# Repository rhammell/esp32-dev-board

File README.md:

# esp32-dev-board
This repository contains the KiCad project files for a custom development board based on the ESP32-S3-WROOM module.

The board features a simplistic design, breaking out GPIO and power pins for easy prototyping, while using only essential components for power and data transfer. 

KiCad project files include the schematic and PCB designs which can be viewed and edited, and a full BOM with LCSC part numbers for sourcing and assembly. 

## Features

* **Core:** ESP32-S3-WROOM-1N8R8 module (8MB Flash + 8MB PSRAM).
* **USB Interface:** USB-C connector utilizing the S3's native USB Serial/JTAG controller.
* **Power:** Integrated 3.3V LDO regulator with a dedicated power LED indicator.
* **Prototyping:** Standard 2.54mm pitch header pins for full GPIO and power breakout.
* **Control:** Physical Reset and Boot buttons for manual flashing mode entry.
* **User IO:** Onboard programmable LED tied to **GPIO 21**.
* **Manufacturing:** Complete BOM included with **LCSC part numbers** for simplified sourcing and assembly.

## Changelog

### v0.2
- Replaced LD1117 with AP2114 3.3V regulator for more stable 3.3V power supply
- Transitioned to higher voltage rated 0805 capacitors on power rails to minimize DC bias capacitance loss

### v0.1
- Initial release of the ESP32-S3-WROOM-1 development board.

## Arduino IDE Setup

To program the **ESP32-S3 Dev Board**, follow these steps to configure your environment.

### 1. Install the ESP32 Board Package
1. Open the Arduino IDE (v2.3.6 or newer recommended).
2. Go to **File > Preferences**.
3. In the **Additional Boards Manager URLs** field, paste the following link:
   `https://espressif.github.io/arduino-esp32/package_esp32_index.json`
4. Go to **Tools > Board > Boards Manager**, search for **esp32**, and install the latest version by **Espressif Systems**.

### 2. Required Board Settings
Because this board uses the **N8R8** module with native USB, you must use the following settings in the **Tools** menu:

| Setting            | Selection                          | Reason                                         |
|--------------------|------------------------------------|------------------------------------------------|
| **Board** | **ESP32S3 Dev Module** | Standard target for S3-WROOM modules.         |
| **USB CDC On Boot**| **Enabled** | **Critical:** Allows Serial Monitor over USB. |
| **Flash Mode** | **QIO 80MHz** | Standard for WROOM modules.                    |
| **Flash Size** | **8MB (64Mb)** | Matches the N8 (8MB Flash) specification.      |
| **PSRAM** | **OPI PSRAM** | Matches the R8 (8MB Octal) specification.     |

---

## Hardware Test Sketch

Use this sketch to verify that your PCB is fully functional. It tests the serial communication, identifies the onboard memory, and blinks the onboard LED on **GPIO 21**.

```cpp
/*
 * ESP32-S3 Dev Board Hardware Test
 * Verifies: Native USB Serial, GPIO 21 (LED), and N8R8 Memory
 */

const int USER_LED = 21;

void setup() {
  // Initialize Serial
  // Native USB: Baud rate is ignored but kept for compatibility
  Serial.begin(115200);
  
  // Set LED pin as output
  pinMode(USER_LED, OUTPUT);

  // Wait 2 seconds so you don't miss the initial serial print
  delay(2000); 

  Serial.println("\n========================================");
  Serial.println("   ESP32-S3 CUSTOM DEV BOARD TEST");
  Serial.println("========================================");

  // Print Flash Size
  uint32_t flashSize = ESP.getFlashChipSize() / (1024 * 1024);
  Serial.printf("Flash Size: %d MB\n", flashSize);

  // Print PSRAM Size
  // If this shows 0MB, ensure 'Tools > PSRAM' is set to 'OPI PSRAM'
  uint32_t psramSize = ESP.getPsramSize() / (1024 * 1024);
  Serial.printf("PSRAM Size: %d MB\n", psramSize);

  if (psramSize > 0) {
    Serial.println("Status: PSRAM detected successfully!");
  } else {
    Serial.println("Status: PSRAM NOT FOUND. Check IDE settings.");
  }
  
  Serial.println("----------------------------------------");
  Serial.println("Beginning LED blink on GPIO 21...");
}

void loop() {
  // Toggle LED and print status
  digitalWrite(USER_LED, HIGH);
  Serial.println("LED: ON");
  delay(1000);

  digitalWrite(USER_LED, LOW);
  Serial.println("LED: OFF");
  delay(1000);
}
```

## Troubleshooting 

* **Failed to Connect:** If the IDE cannot find the board, hold the BOOT button, tap the RESET button, and then release BOOT to force the chip into "Download Mode."

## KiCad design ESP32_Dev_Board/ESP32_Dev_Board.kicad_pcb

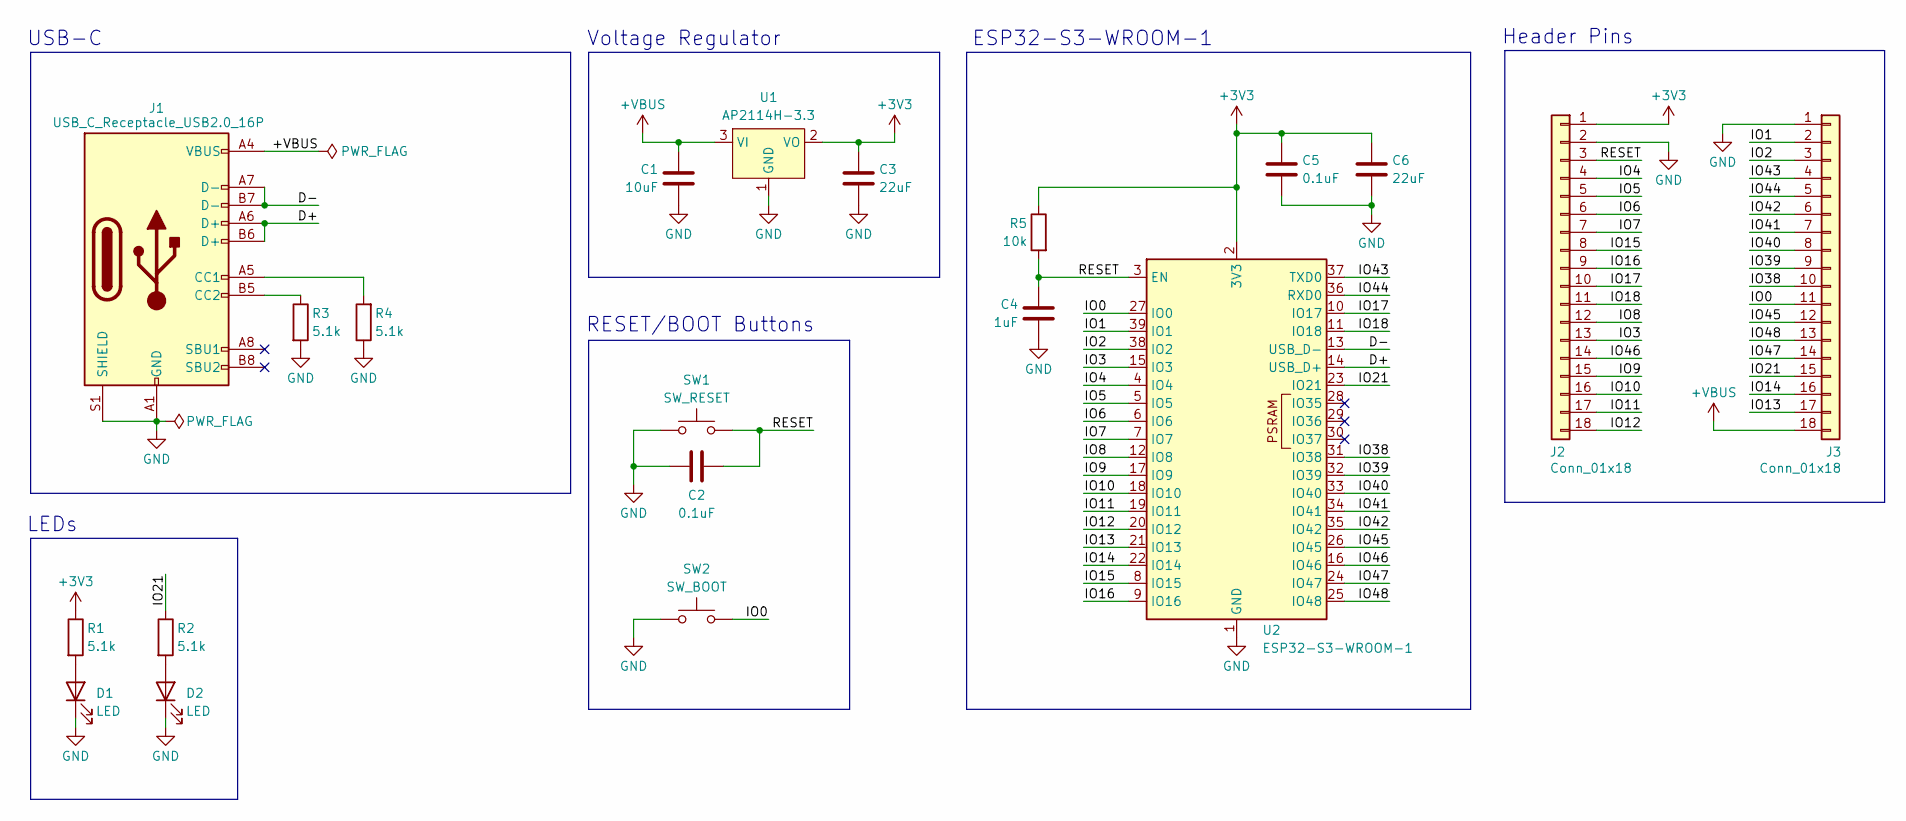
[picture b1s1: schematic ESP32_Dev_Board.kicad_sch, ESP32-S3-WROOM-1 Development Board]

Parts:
C1: 10uF; C_0805_2012Metric; LCSC C15850
C2, C5: 0.1uF; C_0603_1608Metric; LCSC C14663
C3, C6: 22uF; C_0805_2012Metric; LCSC C45783
C4: 1uF; C_0603_1608Metric; LCSC C15849
D1, D2: LED; D_0603_1608Metric; LCSC C2286
J1: USB_C_Receptacle_USB2.0_16P; USB_C_Receptacle_GCT_USB4105-xx-A_16P_TopMnt_Horizontal; LCSC C2988369
J2, J3: Conn_01x18; PinHeader_1x18_P2.54mm_Vertical
R1, R2, R3, R4: 5.1k; R_0603_1608Metric; LCSC C23186
R5: 10k; R_0603_1608Metric; LCSC C25804
SW1: SW_RESET; SW_SPST_TS-1088-xR020; LCSC C720477
SW2: SW_BOOT; SW_SPST_TS-1088-xR020; LCSC C720477
U1: AP2114H-3.3; SOT-223-3_TabPin2; LCSC C150716
U2: ESP32-S3-WROOM-1; LCSC C2913201

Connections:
+3V3: C3.1, C5.1, C6.1, J2.1, R1.1, R5.1, U1.2 (VO), U2.2 (3V3)
+VBUS: C1.1, J1.A4 (VBUS), J1.A9 (VBUS), J1.B4 (VBUS), J1.B9 (VBUS), J3.18, U1.3 (VI)
/D+: J1.A6 (D+), J1.B6 (D+), U2.14 (USB_D+)
/D-: J1.A7 (D-), J1.B7 (D-), U2.13 (USB_D-)
/IO0: J3.11, SW2.2, U2.27 (IO0)
/IO1: J3.2, U2.39 (IO1)
/IO2: J3.3, U2.38 (IO2)
/IO3: J2.13, U2.15 (IO3)
/IO4: J2.4, U2.4 (IO4)
/IO5: J2.5, U2.5 (IO5)
/IO6: J2.6, U2.6 (IO6)
/IO7: J2.7, U2.7 (IO7)
/IO8: J2.12, U2.12 (IO8)
/IO9: J2.15, U2.17 (IO9)
/IO10: J2.16, U2.18 (IO10)
/IO11: J2.17, U2.19 (IO11)
/IO12: J2.18, U2.20 (IO12)
/IO13: J3.17, U2.21 (IO13)
/IO14: J3.16, U2.22 (IO14)
/IO15: J2.8, U2.8 (IO15)
/IO16: J2.9, U2.9 (IO16)
/IO17: J2.10, U2.10 (IO17)
/IO18: J2.11, U2.11 (IO18)
/IO21: J3.15, R2.1, U2.23 (IO21)
/IO38: J3.10, U2.31 (IO38)
/IO39: J3.9, U2.32 (IO39)
/IO40: J3.8, U2.33 (IO40)
/IO41: J3.7, U2.34 (IO41)
/IO42: J3.6, U2.35 (IO42)
/IO43: J3.4, U2.37 (TXD0)
/IO44: J3.5, U2.36 (RXD0)
/IO45: J3.12, U2.26 (IO45)
/IO46: J2.14, U2.16 (IO46)
/IO47: J3.14, U2.24 (IO47)
/IO48: J3.13, U2.25 (IO48)
/RESET: C2.1, C4.1, J2.3, R5.2, SW1.2, U2.3 (EN)
GND: C1.2, C2.2, C3.2, C4.2, C5.2, C6.2, D1.1 (K), D2.1 (K), J1.A1 (GND), J1.A12 (GND), J1.B1 (GND), J1.B12 (GND), J1.S1 (SHIELD), J2.2, J3.1, R3.2, R4.1, SW1.1, SW2.1, U1.1 (GND), U2.1 (GND), U2.40 (GND), U2.41 (GND)
unnamed: D1.2 (A), R1.2
unnamed: D2.2 (A), R2.2
unnamed: J1.A5 (CC1), R4.2
unnamed: J1.B5 (CC2), R3.1

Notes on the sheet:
Voltage Regulator
ESP32-S3-WROOM-1
USB-C
RESET/BOOT Buttons
Header Pins
LEDs

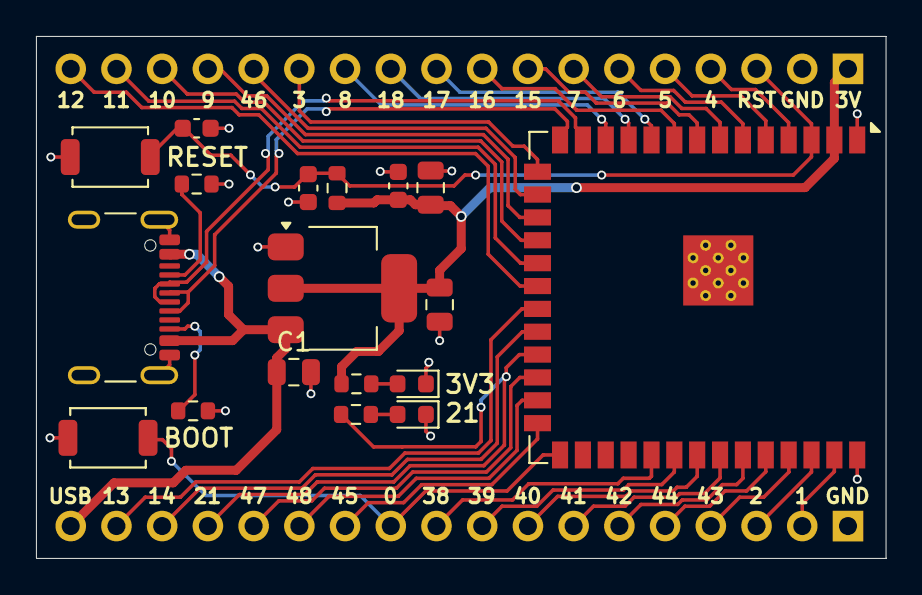
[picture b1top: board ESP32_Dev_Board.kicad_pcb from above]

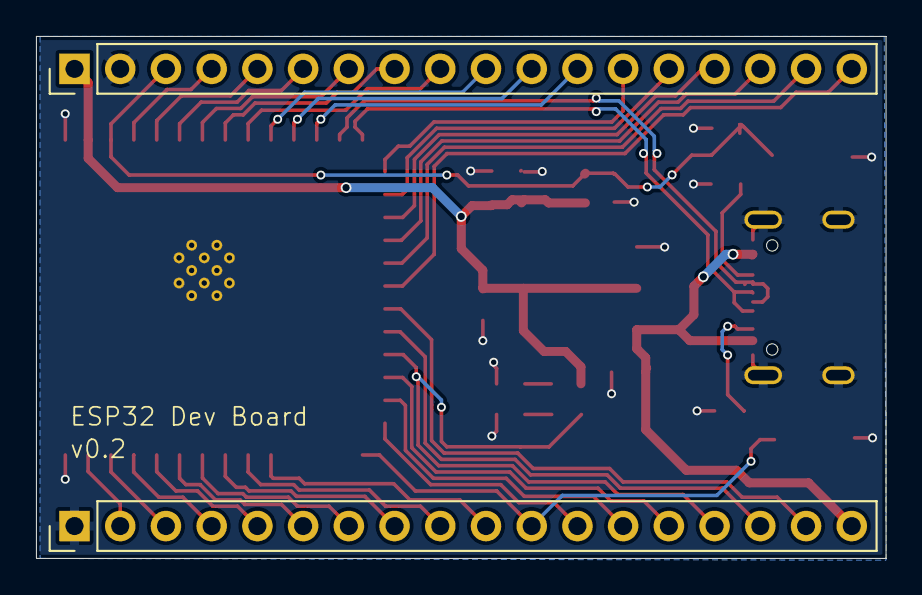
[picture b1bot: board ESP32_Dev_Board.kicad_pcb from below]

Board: 2 copper layers, 47.2 x 29.0 mm, 20 parts (2 on the bottom side), 41 nets.

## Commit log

2025-12-30 Update .gitignore to include macOS specific files
2025-12-30 Initial Kicad project files
2026-01-14 Version 0.1 - Copleted schematic and PCB design for v0.1, including modified component footprints
2026-01-14 Update README.md to include detailed project description and features for the ESP32-S3 dev board, along with images of the board's front and back.
2026-01-25 v0.2 - AP2114 3.3V regulator; Updated capacitor component selection and footprints
